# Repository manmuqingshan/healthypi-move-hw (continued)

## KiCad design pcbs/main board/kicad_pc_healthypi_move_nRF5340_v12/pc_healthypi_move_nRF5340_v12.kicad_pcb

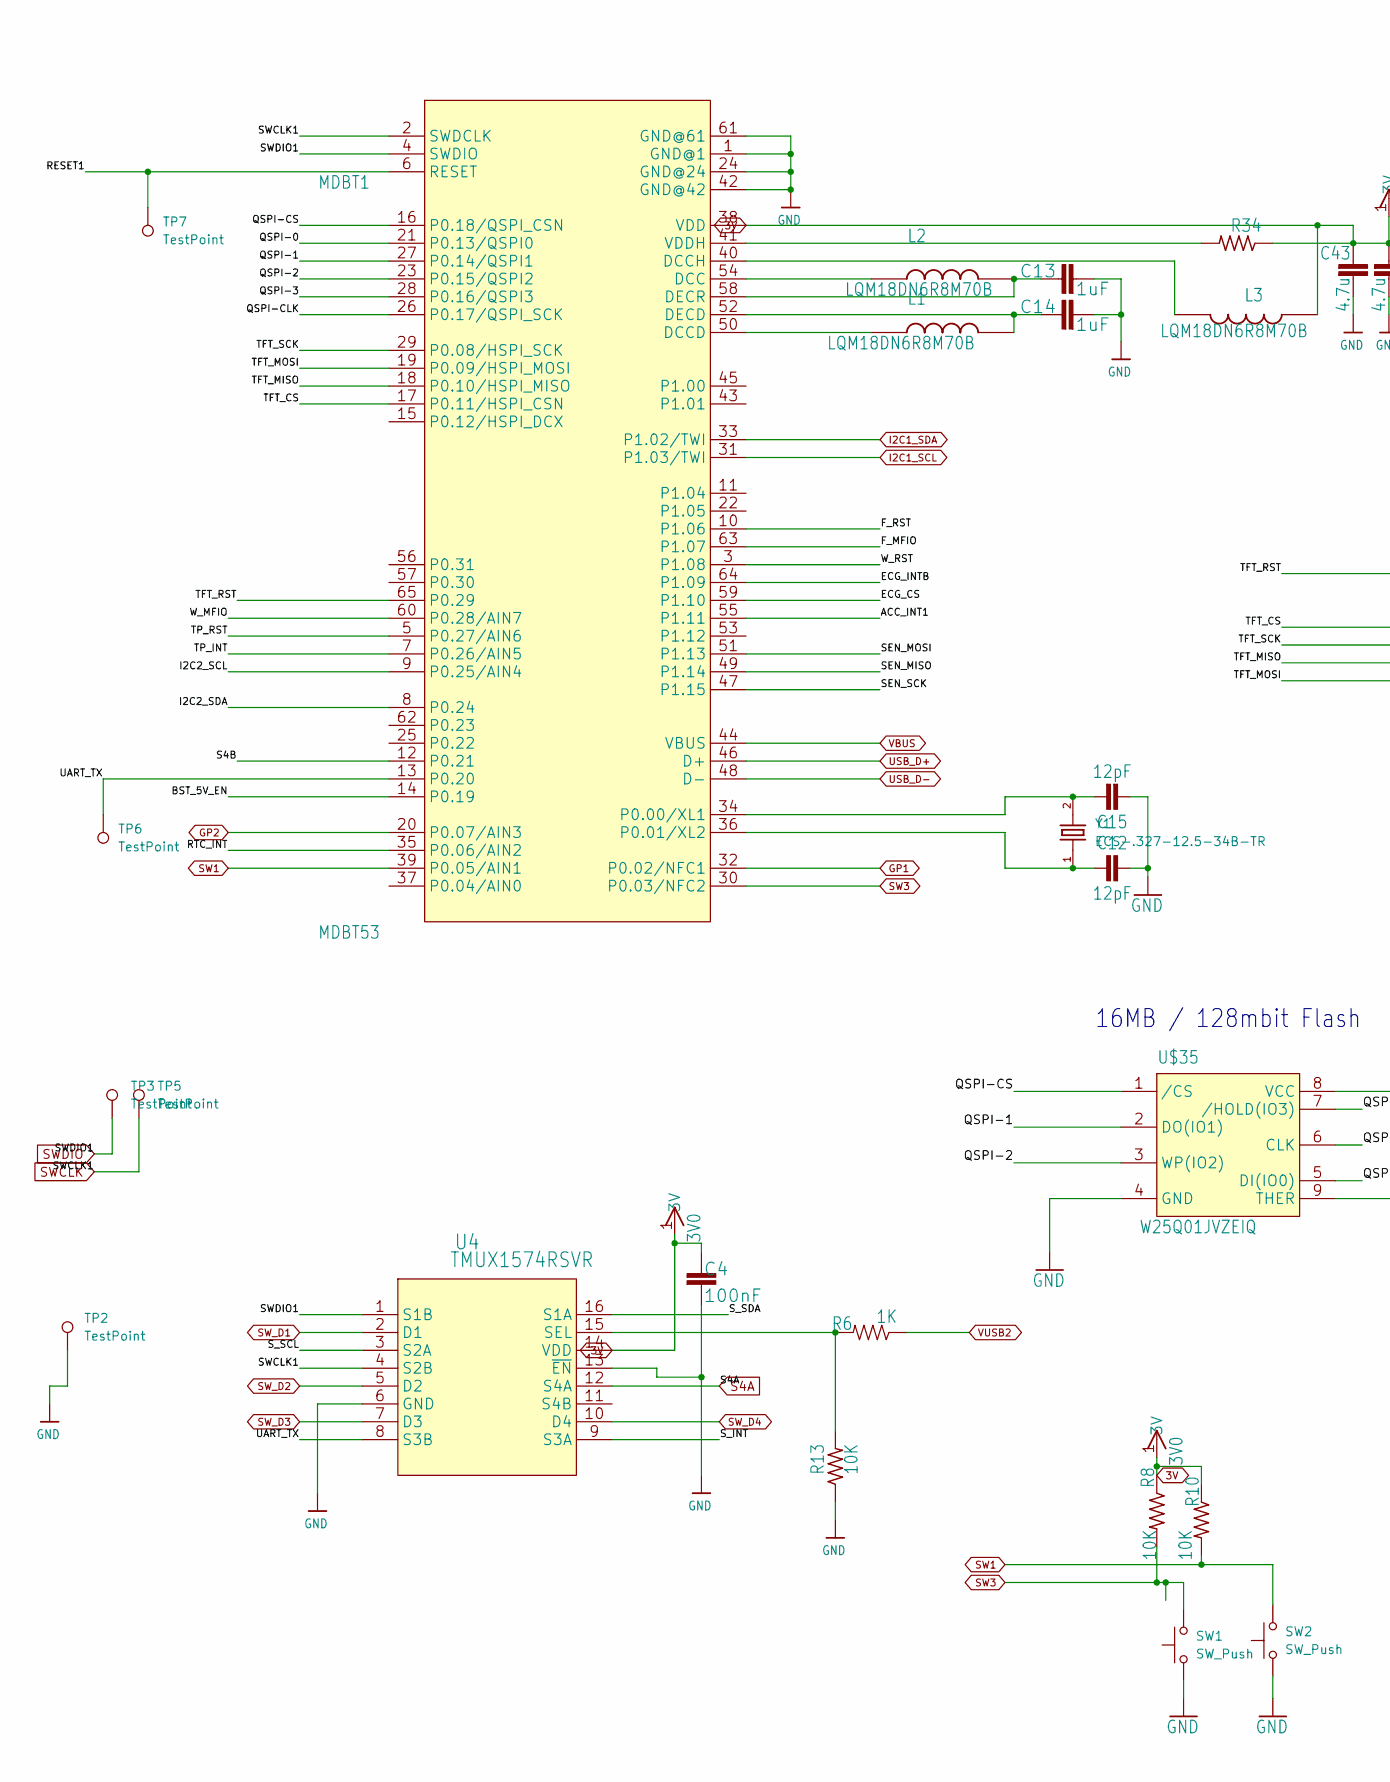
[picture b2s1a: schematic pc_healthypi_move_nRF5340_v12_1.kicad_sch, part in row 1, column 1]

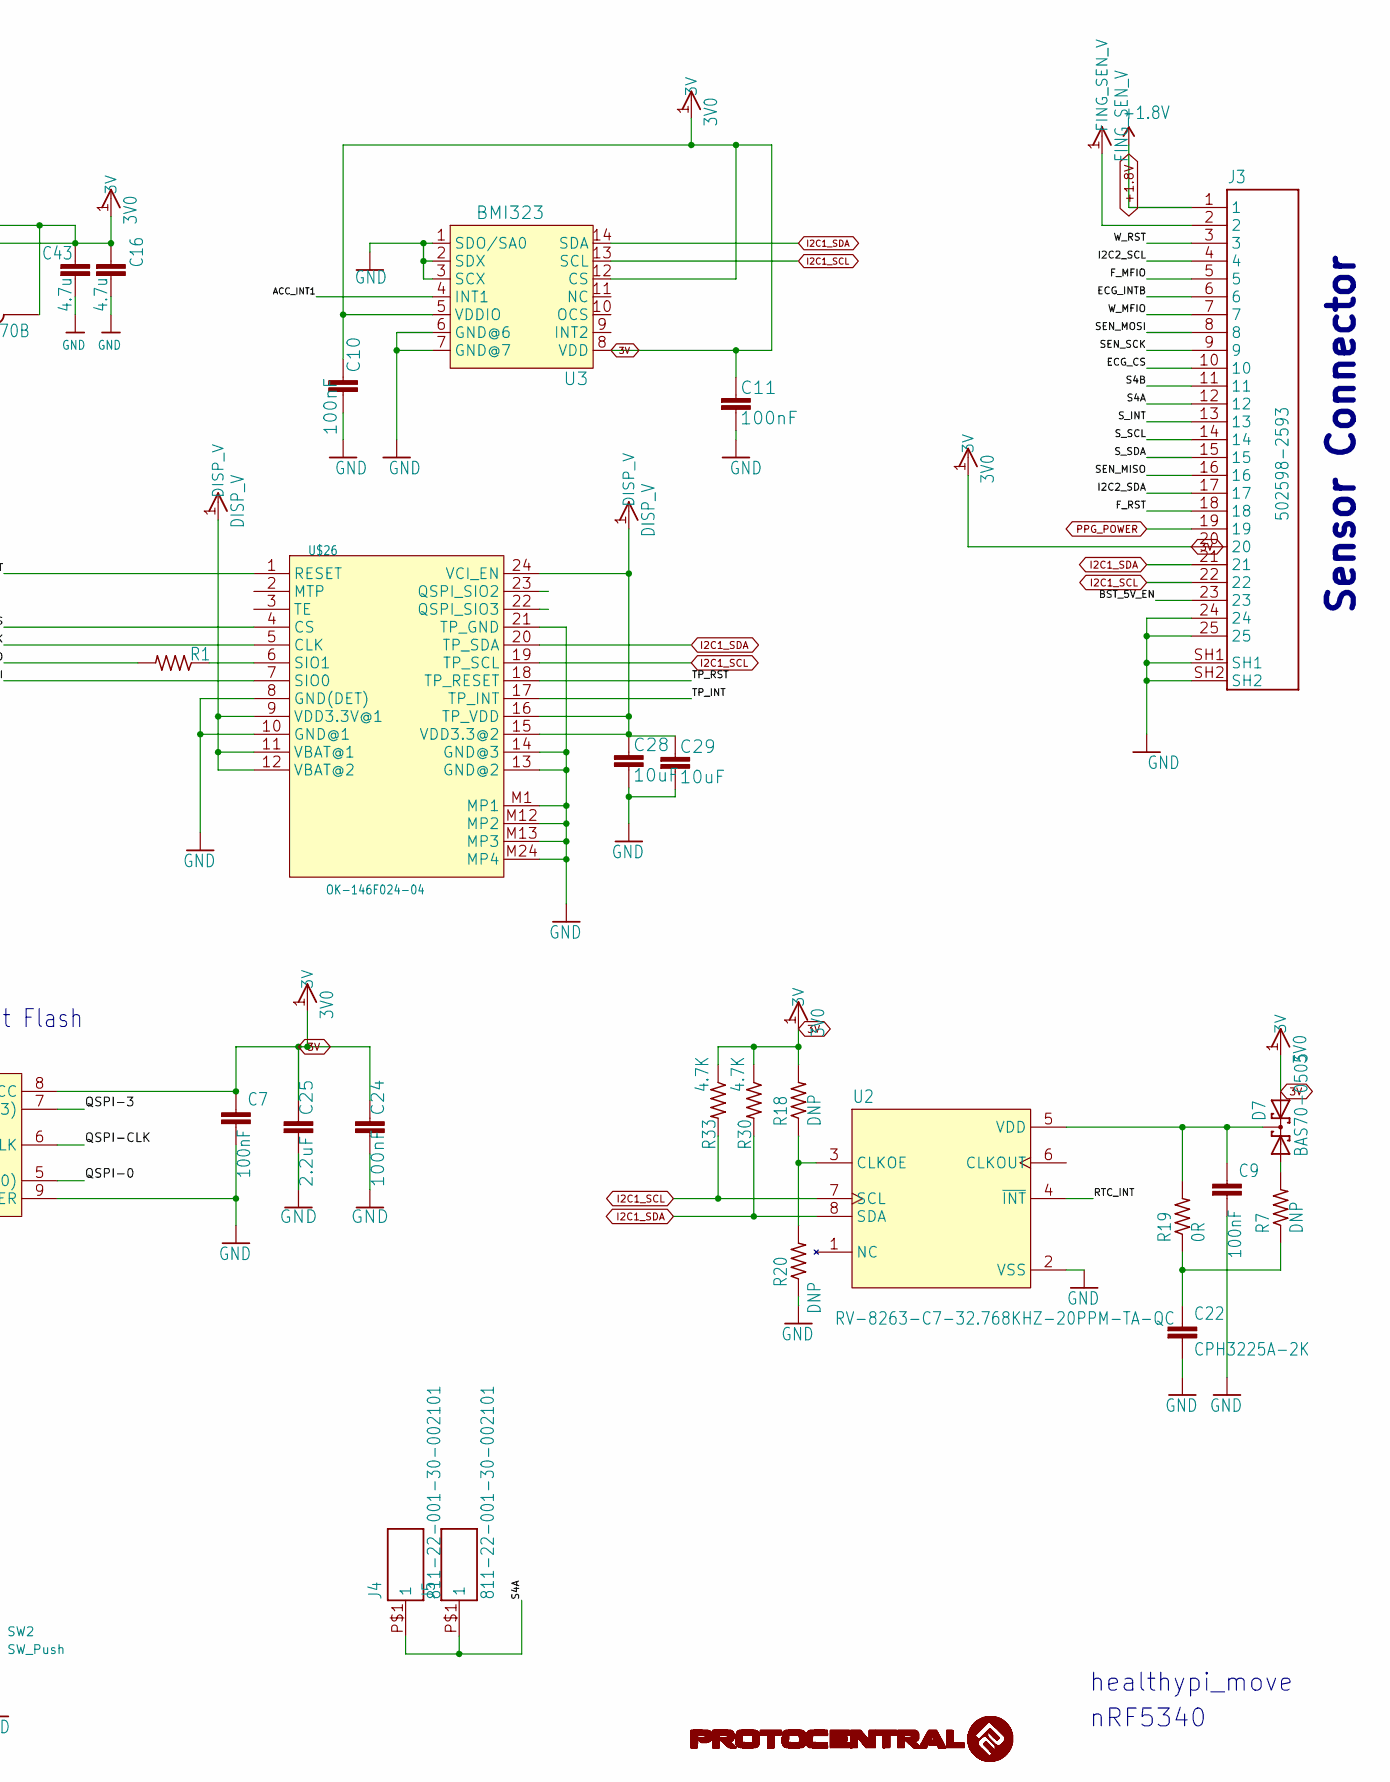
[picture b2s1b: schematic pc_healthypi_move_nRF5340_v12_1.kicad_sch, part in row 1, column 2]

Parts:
C4, C7, C9, C10, C11, C24: 100nF; C_0402_1005Metric
C12, C15: 12pF; C_0402_1005Metric
C13, C14: 1uF; C_0402_1005Metric
C16, C43: 4.7u; C_0402_1005Metric
C22: CPH3225A-2K; C_1210_3225Metric
C25: 2.2uF; C_0402_1005Metric
C28, C29: 10uF; C_0402_1005Metric
D7: BAS70-0505; D_SOD-323
J3: 502598-2593; AMPHENOL_F14D-1B7H1-E8C25
J4, J5: 811-22-001-30-002101; MILL_MAX_821-22-001
L1, L2, L3: LQM18DN6R8M70B; INDC1608X95N
MDBT1: MDBT53; MDBT53-1M_RAY
R1, R34: 220R; R_0402_1005Metric
R6: 1K; R_0402_1005Metric
R7, R18, R20: DNP; R_0402_1005Metric
R8, R10, R13: 10K; R_0402_1005Metric
R19: 0R; R_0402_1005Metric
R30, R33: 4.7K; R_0402_1005Metric
SW1, SW2: SW_Push; Panasonic_EVQPUL_EVQPUC
TP2, TP3, TP5, TP6, TP7: TestPoint; TestPoint_Pad_1.0x1.0mm
U2: RV-8263-C7-32.768KHZ-20PPM-TA-QC; IC_RV-8263-C7-32.768KHZ-20PPM-TA-QC
U3: BMI323; Bosch_LGA-14_3x2.5mm_P0.5mm
U4: TMUX1574RSVR; UQFN-16_1.8x2.6mm_P0.4mm
U$26: OK-146F024-04
U$35: W25Q01JVZEIQ; WSON-8-1EP_8x6mm_P1.27mm_EP3.4x4.3mm
Y1: ECS-.327-12.5-34B-TR; XTAL_ECS-31B_ECS

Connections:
3V: C4.1, C7.1, C10.1, C11.1, C16.1, C24.1, C25.1, C43.1, D7.2 (A2), J3.20, L3.1, MDBT1.38 (VDD), R8.1, R10.1, R18.2, R30.1, R33.1, R34.1, U3.5 (VDDIO), U3.8 (VDD), U3.12 (CS), U4.14 (VDD), U$35.8 (VCC); also elsewhere on the board
+1.8V: J3.1; also elsewhere on the board
/pc_healthypi_move_nRF5340_v10_1/ACC_INT1: MDBT1.55 (P1.11), U3.4 (INT1)
/pc_healthypi_move_nRF5340_v10_1/BST_5V_EN: J3.23, MDBT1.14 (P0.19)
/pc_healthypi_move_nRF5340_v10_1/ECG_CS: J3.10, MDBT1.59 (P1.10)
/pc_healthypi_move_nRF5340_v10_1/ECG_INTB: J3.6, MDBT1.64 (P1.09)
/pc_healthypi_move_nRF5340_v10_1/F_MFIO: J3.5, MDBT1.63 (P1.07)
/pc_healthypi_move_nRF5340_v10_1/F_RST: J3.18, MDBT1.10 (P1.06)
/pc_healthypi_move_nRF5340_v10_1/I2C2_SCL: J3.4, MDBT1.9 (P0.25/AIN4)
/pc_healthypi_move_nRF5340_v10_1/I2C2_SDA: J3.17, MDBT1.8 (P0.24)
/pc_healthypi_move_nRF5340_v10_1/QSPI-0: MDBT1.21 (P0.13/QSPI0), U$35.5 (DI(IO0))
/pc_healthypi_move_nRF5340_v10_1/QSPI-1: MDBT1.27 (P0.14/QSPI1), U$35.2 (DO(IO1))
/pc_healthypi_move_nRF5340_v10_1/QSPI-2: MDBT1.23 (P0.15/QSPI2), U$35.3 (WP(IO2))
/pc_healthypi_move_nRF5340_v10_1/QSPI-3: MDBT1.28 (P0.16/QSPI3), U$35.7 (/HOLD(IO3))
/pc_healthypi_move_nRF5340_v10_1/QSPI-CLK: MDBT1.26 (P0.17/QSPI_SCK), U$35.6 (CLK)
/pc_healthypi_move_nRF5340_v10_1/QSPI-CS: MDBT1.16 (P0.18/QSPI_CSN), U$35.1 (/CS)
/pc_healthypi_move_nRF5340_v10_1/RESET1: MDBT1.6 (RESET), TP7.1
/pc_healthypi_move_nRF5340_v10_1/RTC_INT: MDBT1.35 (P0.06/AIN2), U2.4 (~INT)
/pc_healthypi_move_nRF5340_v10_1/S4B: J3.11, MDBT1.12 (P0.21)
/pc_healthypi_move_nRF5340_v10_1/SEN_MISO: J3.16, MDBT1.49 (P1.14)
/pc_healthypi_move_nRF5340_v10_1/SEN_MOSI: J3.8, MDBT1.51 (P1.13)
/pc_healthypi_move_nRF5340_v10_1/SEN_SCK: J3.9, MDBT1.47 (P1.15)
/pc_healthypi_move_nRF5340_v10_1/S_INT: J3.13, U4.9 (S3A)
/pc_healthypi_move_nRF5340_v10_1/S_SCL: J3.14, U4.3 (S2A)
/pc_healthypi_move_nRF5340_v10_1/S_SDA: J3.15, U4.16 (S1A)
/pc_healthypi_move_nRF5340_v10_1/TFT_CS: MDBT1.17 (P0.11/HSPI_CSN), U$26.4 (CS)
/pc_healthypi_move_nRF5340_v10_1/TFT_MISO: MDBT1.18 (P0.10/HSPI_MISO), R1.2
/pc_healthypi_move_nRF5340_v10_1/TFT_MOSI: MDBT1.19 (P0.09/HSPI_MOSI), U$26.7 (SIO0)
/pc_healthypi_move_nRF5340_v10_1/TFT_RST: MDBT1.65 (P0.29), U$26.1 (RESET)
/pc_healthypi_move_nRF5340_v10_1/TFT_SCK: MDBT1.29 (P0.08/HSPI_SCK), U$26.5 (CLK)
/pc_healthypi_move_nRF5340_v10_1/TP_INT: MDBT1.7 (P0.26/AIN5), U$26.17 (TP_INT)
/pc_healthypi_move_nRF5340_v10_1/TP_RST: MDBT1.5 (P0.27/AIN6), U$26.18 (TP_RESET)
/pc_healthypi_move_nRF5340_v10_1/UART_TX: MDBT1.13 (P0.20), TP6.1, U4.8 (S3B)
/pc_healthypi_move_nRF5340_v10_1/W_MFIO: J3.7, MDBT1.60 (P0.28/AIN7)
/pc_healthypi_move_nRF5340_v10_1/W_RST: J3.3, MDBT1.3 (P1.08)
DISP_V: C28.1, C29.1, U$26.9 (VDD3.3V@1), U$26.11 (VBAT@1), U$26.12 (VBAT@2), U$26.15 (VDD3.3@2), U$26.16 (TP_VDD), U$26.24 (VCI_EN); also elsewhere on the board
FING_SEN_V: J3.2; also elsewhere on the board
GND: C4.2, C7.2, C9.2, C10.2, C11.2, C12.2, C13.2, C14.2, C15.1, C16.2, C22.2, C24.2, C25.2, C28.2, C29.2, C43.2, J3.24, J3.25, J3.SH1, J3.SH2, MDBT1.1 (GND@1), MDBT1.24 (GND@24), MDBT1.42 (GND@42), MDBT1.61 (GND@61), R13.1, R20.1, SW1.1, SW2.1, TP2.1, U2.2 (VSS), U3.1 (SDO/SA0), U3.2 (SDX), U3.3 (SCX), U3.6 (GND@6), U3.7 (GND@7), U4.6 (GND), U4.13 (~EN), U$26.8 (GND(DET)), U$26.10 (GND@1), U$26.13 (GND@2), U$26.14 (GND@3), U$26.21 (TP_GND), U$26.M1 (MP1), U$26.M12 (MP2), U$26.M13 (MP3), U$26.M24 (MP4), U$35.4 (GND), U$35.9 (THER); also elsewhere on the board
GP1: MDBT1.32 (P0.02/NFC1); also elsewhere on the board
GP2: MDBT1.20 (P0.07/AIN3); also elsewhere on the board
I2C1_SCL: J3.22, MDBT1.31 (P1.03/TWI), R33.2, U2.7 (SCL), U3.13 (SCL), U$26.19 (TP_SCL); also elsewhere on the board
I2C1_SDA: J3.21, MDBT1.33 (P1.02/TWI), R30.2, U2.8 (SDA), U3.14 (SDA), U$26.20 (TP_SDA); also elsewhere on the board
unnamed: C22.1, R7.1, R19.1
unnamed: D7.1 (A1), R7.2
unnamed: C9.1, D7.3 (K1K2), R19.2, U2.5 (VDD)
unnamed: L2.1, MDBT1.54 (DCC)
unnamed: L1.1, MDBT1.50 (DCCD)
unnamed: L3.2, MDBT1.40 (DCCH)
unnamed: C14.1, L1.2, MDBT1.52 (DECD)
unnamed: C13.1, L2.2, MDBT1.58 (DECR)
unnamed: C15.2, MDBT1.34 (P0.00/XL1), Y1.2
unnamed: C12.1, MDBT1.36 (P0.01/XL2), Y1.1
unnamed: MDBT1.41 (VDDH), R34.2
unnamed: R18.1, R20.2, U2.3 (CLKOE)
unnamed: R6.2, R13.2, U4.15 (SEL)
unnamed: R1.1, U$26.6 (SIO1)
PPG_POWER: J3.19; also elsewhere on the board
S4A: J3.12, J4.P$1 (1), J5.P$1 (1), U4.12 (S4A)
SW1: MDBT1.39 (P0.05/AIN1), R10.2, SW2.2; also elsewhere on the board
SW3: MDBT1.30 (P0.03/NFC2), R8.2, SW1.2; also elsewhere on the board
SWCLK: MDBT1.2 (SWDCLK), TP5.1, U4.4 (S2B)
SWDIO: MDBT1.4 (SWDIO), TP3.1, U4.1 (S1B)
SW_D1: U4.2 (D1); also elsewhere on the board
SW_D2: U4.5 (D2); also elsewhere on the board
SW_D3: U4.7 (D3); also elsewhere on the board
SW_D4: U4.10 (D4); also elsewhere on the board
USB_D+: MDBT1.46 (D+); also elsewhere on the board
USB_D-: MDBT1.48 (D-); also elsewhere on the board
VBUS: MDBT1.44 (VBUS); also elsewhere on the board
VUSB2: R6.1; also elsewhere on the board

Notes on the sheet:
16MB / 128mbit Flash
Sensor Connector
nRF5340
healthypi_move

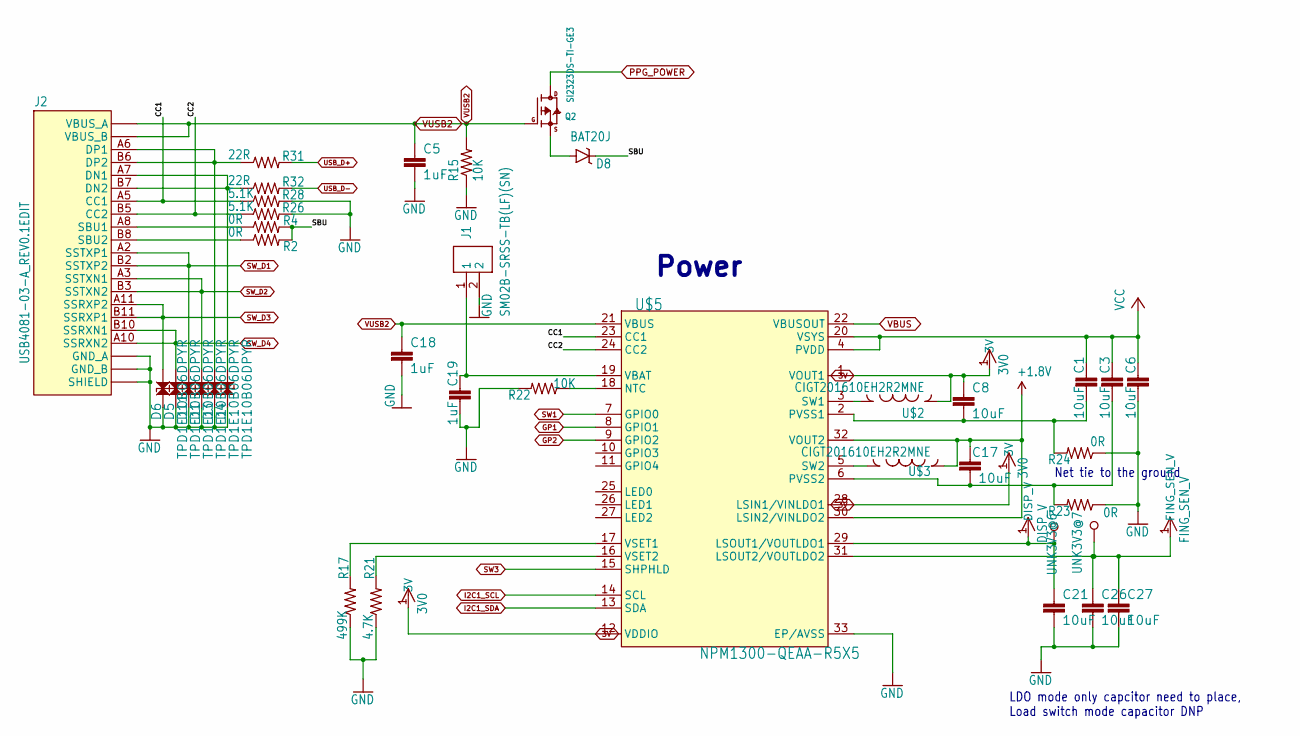
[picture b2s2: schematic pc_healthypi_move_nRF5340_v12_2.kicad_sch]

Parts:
C1, C3, C6, C8, C17, C21, C26, C27: 10uF; C_0402_1005Metric
C5, C18, C19: 1uF; C_0402_1005Metric
D1, D3, D4, D5, D6, D11: TPD1E10B06DPYR; D_0402_1005Metric
D8: BAT20J; D_SOD-323
J1: SM02B-SRSS-TB(LF)(SN); JST_SH_SM02B-SRSS-TB_1x02-1MP_P1.00mm_Horizontal
J2: USB4081-03-A_REV0.1EDIT; GCT_USB4081-03-A_REV0.1
Q2: SI2323DS-TI-GE3; SOT23-R
R2, R4, R23, R24: 0R; R_0402_1005Metric
R15, R22: 10K; R_0402_1005Metric
R17: 499K; R_0402_1005Metric
R21: 4.7K; R_0402_1005Metric
R26, R28: 5.1K; R_0402_1005Metric
R31, R32: 22R; R_0402_1005Metric
U$2, U$3: CIGT201610EH2R2MNE; IND_VLS201610ET-100M
U$5: NPM1300-QEAA-R5X5; QFN32_5X5MC_MCH
UNK3V3@6, UNK3V3@7: TPSQTP13SQ; TestPoint_Pad_1.0x1.0mm

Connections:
3V: C8.1, U$2.2, U$5.1 (VOUT1), U$5.12 (VDDIO), U$5.28 (LSIN1/VINLDO1); also elsewhere on the board
+1.8V: C17.1, U$3.2, U$5.30 (LSIN2/VINLDO2), U$5.32 (VOUT2); also elsewhere on the board
/pc_healthypi_move_nRF5340_v10_2/CC1: J2.A5 (CC1), R28.1, U$5.23 (CC1)
/pc_healthypi_move_nRF5340_v10_2/CC2: J2.B5 (CC2), R26.1, U$5.24 (CC2)
/pc_healthypi_move_nRF5340_v10_2/SBU: D8.C, R2.2, R4.2
DISP_V: C21.1, U$5.29 (LSOUT1/VOUTLDO1), UNK3V3@6.1; also elsewhere on the board
FING_SEN_V: C26.1, C27.1, U$5.31 (LSOUT2/VOUTLDO2), UNK3V3@7.1; also elsewhere on the board
GND: C5.2, C6.2, C18.2, C19.2, C21.2, C26.2, C27.2, D1.1, D3.1, D4.1, D5.1, D6.1, D11.1, J1.2, J2.A1 (GND_A), J2.A12 (GND_A), J2.B1 (GND_B), J2.B12 (GND_B), J2.P1 (SHIELD), J2.P2 (SHIELD), J2.P3 (SHIELD), J2.P4 (SHIELD), J2.P5 (SHIELD), J2.P6 (SHIELD), J2.P7 (SHIELD), J2.P8 (SHIELD), J2.S5 (SHIELD), J2.S6 (SHIELD), R15.1, R17.1, R21.1, R22.2, R23.1, R24.1, R26.2, R28.2, U$5.33 (EP/AVSS); also elsewhere on the board
GP1: U$5.8 (GPIO1); also elsewhere on the board
GP2: U$5.9 (GPIO2); also elsewhere on the board
I2C1_SCL: U$5.14 (SCL); also elsewhere on the board
I2C1_SDA: U$5.13 (SDA); also elsewhere on the board
unnamed: D4.2, J2.A7 (DN1), J2.B7 (DN2), R32.1
unnamed: D3.2, J2.A6 (DP1), J2.B6 (DP2), R31.1
unnamed: J2.A8 (SBU1), R4.1
unnamed: J2.B8 (SBU2), R2.1
unnamed: D8.A, Q2.2 (S)
unnamed: R22.1, U$5.18 (NTC)
unnamed: C1.2, C8.2, R24.2, U$5.2 (PVSS1)
unnamed: C3.2, C17.2, R23.2, U$5.6 (PVSS2)
unnamed: U$2.1, U$5.3 (SW1)
unnamed: U$3.1, U$5.5 (SW2)
unnamed: C19.1, J1.1, U$5.19 (VBAT)
unnamed: R17.2, U$5.17 (VSET1)
unnamed: R21.2, U$5.16 (VSET2)
PPG_POWER: Q2.3 (D); also elsewhere on the board
SW1: U$5.7 (GPIO0); also elsewhere on the board
SW3: U$5.15 (SHPHLD); also elsewhere on the board
SW_D1: D11.2, J2.A2 (SSTXP1), J2.B2 (SSTXP2); also elsewhere on the board
SW_D2: D1.2, J2.A3 (SSTXN1), J2.B3 (SSTXN2); also elsewhere on the board
SW_D3: D6.2, J2.A11 (SSRXP2), J2.B11 (SSRXP1); also elsewhere on the board
SW_D4: D5.2, J2.A10 (SSRXN2), J2.B10 (SSRXN1); also elsewhere on the board
USB_D+: R31.2; also elsewhere on the board
USB_D-: R32.2; also elsewhere on the board
VBUS: U$5.22 (VBUSOUT); also elsewhere on the board
VCC: C1.1, C3.1, C6.1, U$5.4 (PVDD), U$5.20 (VSYS)
VUSB2: C5.1, C18.1, J2.A4 (VBUS_A), J2.A9 (VBUS_A), J2.B4 (VBUS_B), J2.B9 (VBUS_B), Q2.1 (G), R15.2, U$5.21 (VBUS); also elsewhere on the board

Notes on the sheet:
Power
Net tie to the ground
LDO mode only capcitor need to place, Load switch mode capacitor DNP

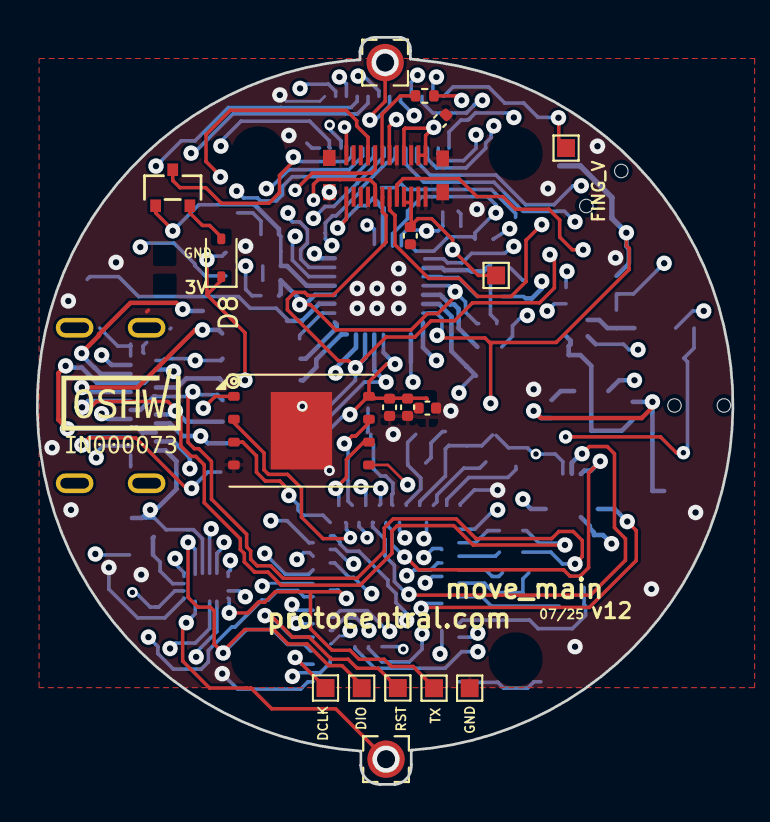
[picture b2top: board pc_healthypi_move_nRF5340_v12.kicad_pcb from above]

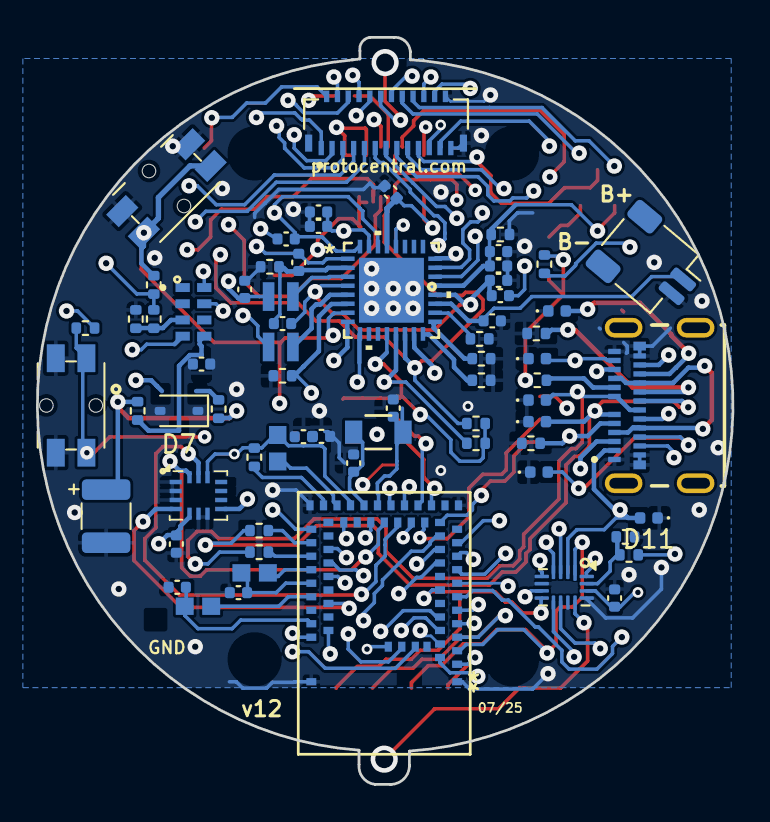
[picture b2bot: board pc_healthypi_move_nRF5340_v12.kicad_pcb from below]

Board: 6 copper layers, 38.6 x 41.5 mm, 87 parts (68 on the bottom side), 86 nets.

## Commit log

2025-09-25 Added latest version of PCBs
2025-09-25 Updated README with latest info
